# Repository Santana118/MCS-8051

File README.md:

# MCS-8051

Almost everything is written in assembly language for MCS 8051. Just copy this source file into Proteus 8 for simulating MCS 8051 component or you can upload it into your own physical MCS 8051, but make sure to convert this source file into BIN format first.

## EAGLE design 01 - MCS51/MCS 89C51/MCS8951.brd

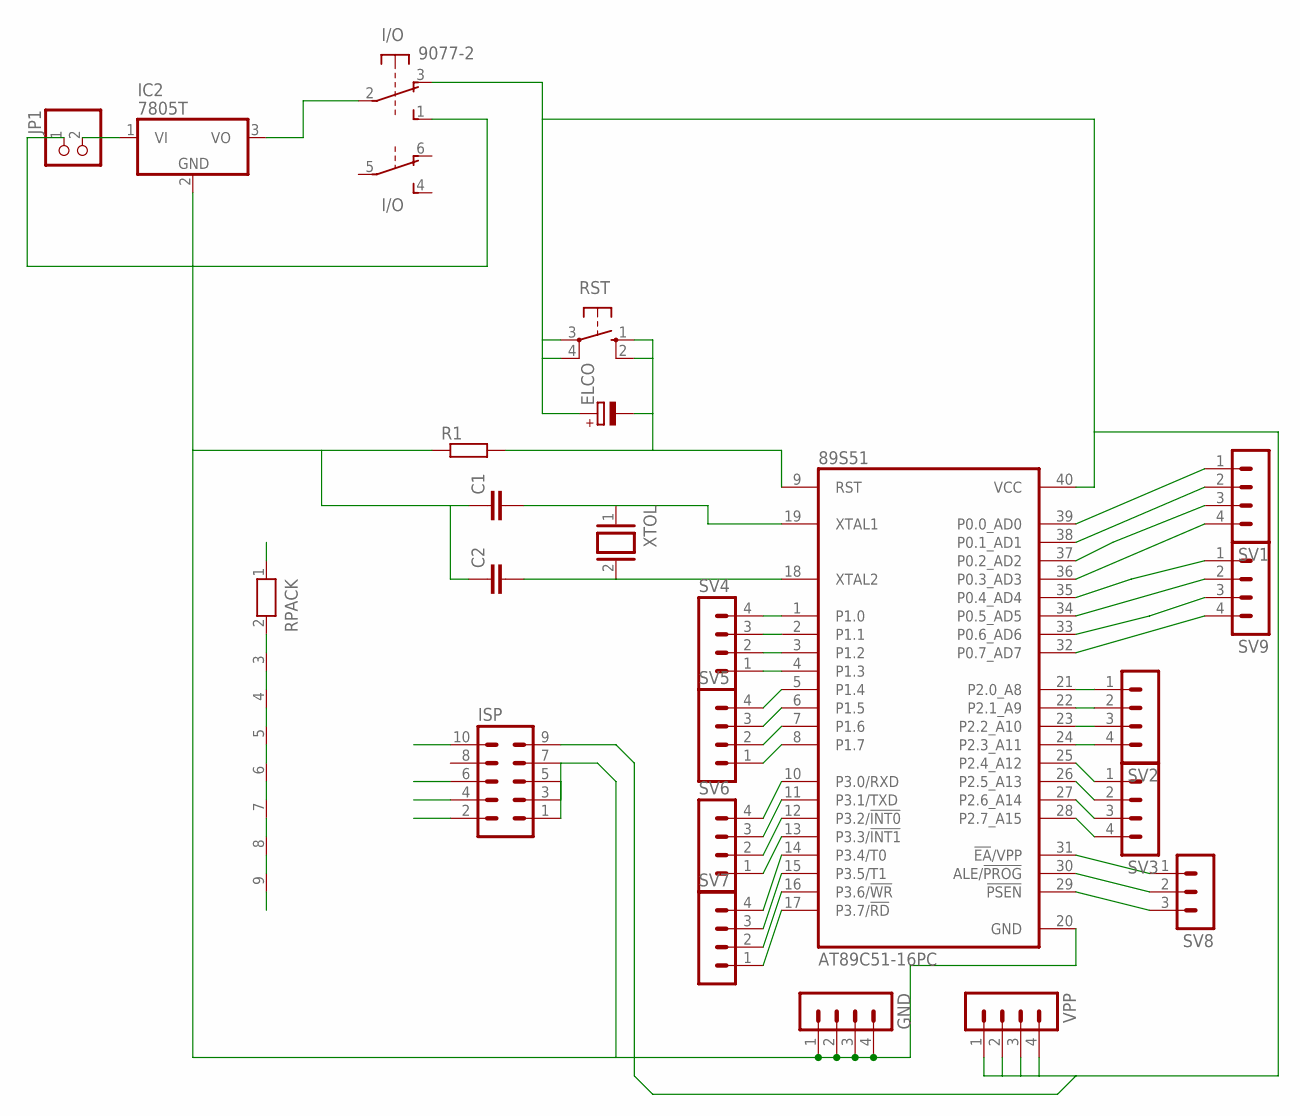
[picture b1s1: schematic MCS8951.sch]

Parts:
89S51: AT89C51-16PC; DIL40
C1, C2: C-EU025-030X050; C025-030X050
ELCO: CPOL-EUE5-5; E5-5
GND: MA04-1
I/O: 9077-2
IC2: 7805T; TO220H
ISP: MA05-2
JP1: PINHD-1X2; 1X02
R1: R-EU_0207/10; 0207/10
RPACK: RN08; RN-9
RST: 10-XX; B3F-10XX
SV1, SV2, SV3, SV4, SV5, SV6, SV7, SV9: MA04-1
SV8: MA03-1
VPP: MA04-1
XTOL: XTAL/S; QS

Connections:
GND: 89S51.20 (GND), C1.1, C2.1, GND.1, GND.2, GND.3, GND.4, I/O.1 (S), IC2.2 (GND), ISP.1, ISP.3, ISP.5, ISP.7, JP1.1, R1.1
MISO: 89S51.7 (P1.6), ISP.2, SV5.2
MOSI: 89S51.6 (P1.5), ISP.10, SV5.3
unnamed: I/O.2, IC2.3 (VO)
unnamed: 89S51.21 (P2.0_A8), SV2.1
unnamed: 89S51.22 (P2.1_A9), SV2.2
unnamed: 89S51.23 (P2.2_A10), SV2.3
unnamed: 89S51.24 (P2.3_A11), SV2.4
unnamed: 89S51.25 (P2.4_A12), SV3.1
unnamed: 89S51.26 (P2.5_A13), SV3.2
unnamed: 89S51.27 (P2.6_A14), SV3.3
unnamed: 89S51.28 (P2.7_A15), SV3.4
unnamed: 89S51.4 (P1.3), SV4.1
unnamed: 89S51.3 (P1.2), SV4.2
unnamed: 89S51.2 (P1.1), SV4.3
unnamed: 89S51.1 (P1.0), SV4.4
unnamed: 89S51.5 (P1.4), SV5.4
unnamed: 89S51.13 (P3.3/!INT1), SV6.1
unnamed: 89S51.12 (P3.2/!INT0), SV6.2
unnamed: 89S51.11 (P3.1/TXD), SV6.3
unnamed: 89S51.10 (P3.0/RXD), SV6.4
unnamed: 89S51.17 (P3.7/!RD), SV7.1
unnamed: 89S51.16 (P3.6/!WR), SV7.2
unnamed: 89S51.15 (P3.5/T1), SV7.3
unnamed: 89S51.14 (P3.4/T0), SV7.4
unnamed: 89S51.31 (!EA!/VPP), SV8.1
unnamed: 89S51.30 (ALE/!PROG), SV8.2
unnamed: 89S51.29 (!PSEN), SV8.3
unnamed: 89S51.19 (XTAL1), C1.2, XTOL.1
unnamed: IC2.1 (VI), JP1.2
unnamed: 89S51.18 (XTAL2), C2.2, XTOL.2
R1: 89S51.39 (P0.0_AD0), RPACK.2, SV1.1
R2: 89S51.38 (P0.1_AD1), RPACK.3, SV1.2
R3: 89S51.37 (P0.2_AD2), RPACK.4, SV1.3
R4: 89S51.36 (P0.3_AD3), RPACK.5, SV1.4
R5: 89S51.35 (P0.4_AD4), RPACK.6, SV9.1
R6: 89S51.34 (P0.5_AD5), RPACK.7, SV9.2
R7: 89S51.33 (P0.6_AD6), RPACK.8, SV9.3
R8: 89S51.32 (P0.7_AD7), RPACK.9, SV9.4
RST: 89S51.9 (RST), ELCO.-, ISP.6, R1.2, RST.1 (S), RST.2 (S1)
SCK: 89S51.8 (P1.7), ISP.4, SV5.1
VPP: 89S51.40 (VCC), ELCO.+, I/O.3 (O), ISP.9, RPACK.1, RST.3, RST.4 (P1), VPP.1, VPP.2, VPP.3, VPP.4

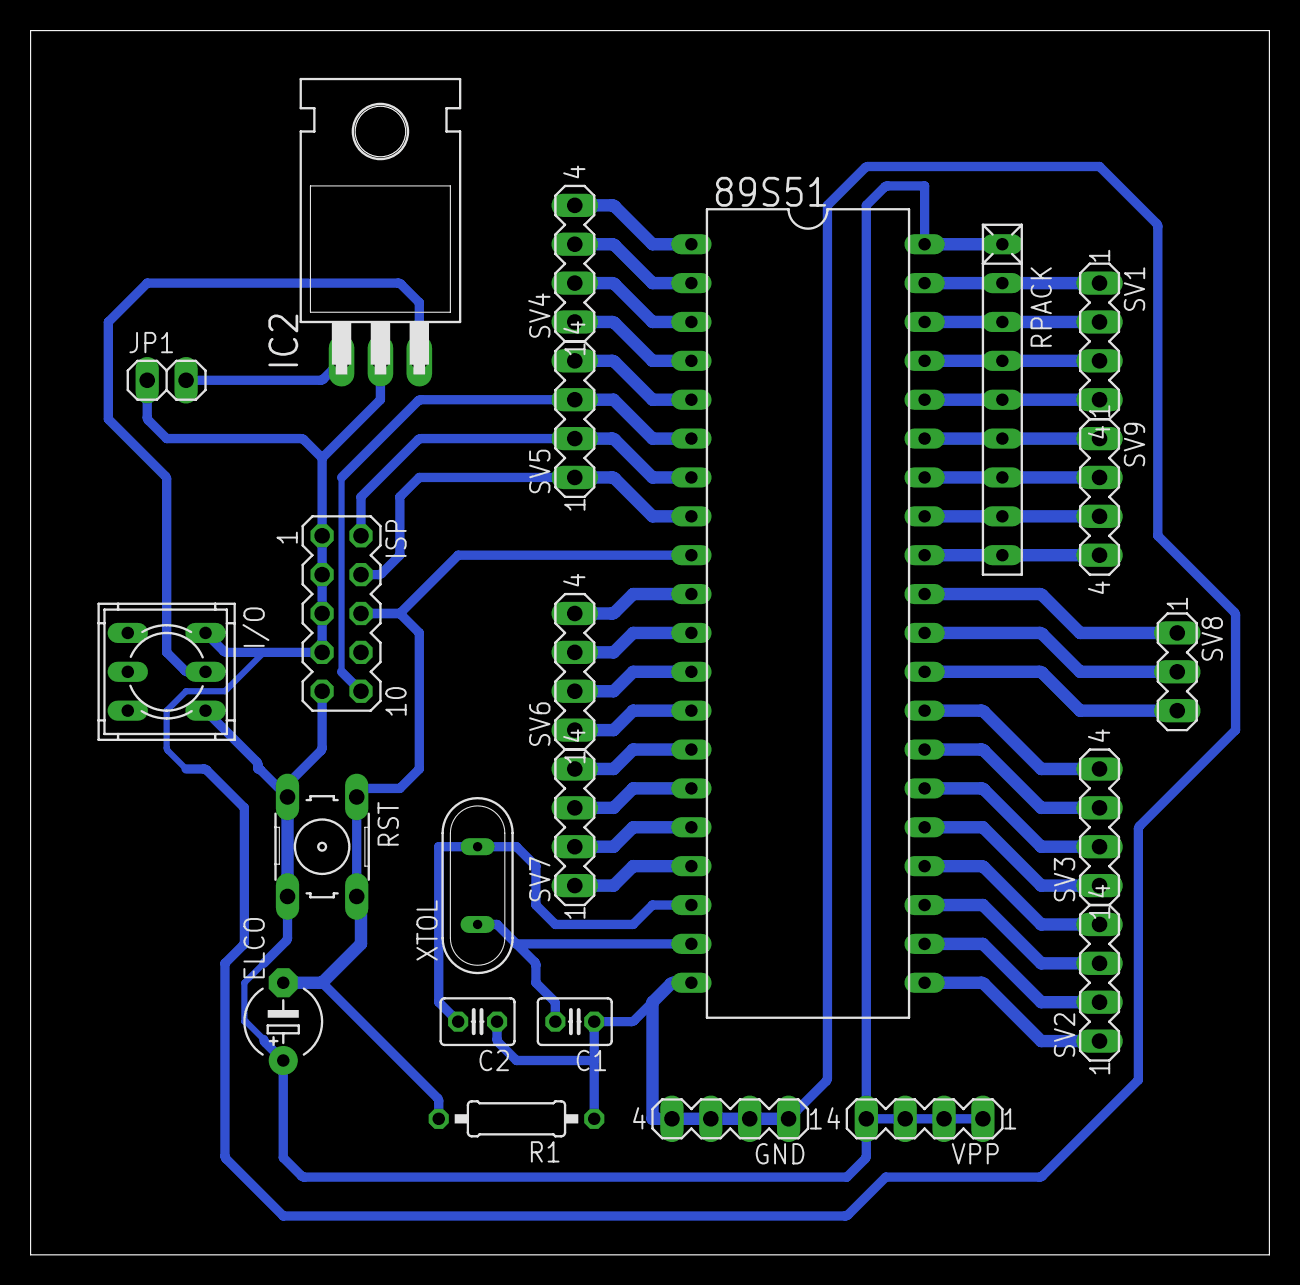
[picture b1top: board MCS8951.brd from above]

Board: 2 copper layers, 81.0 x 80.0 mm, 23 parts (0 on the bottom side), 42 nets.

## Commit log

2020-10-24 Rename 05 - Hexapod.txt to 05 - Quadruped.txt
2020-10-24 Rename 06 - Hexapod with Magnetometer.txt to 06 - Quadruped with Magnetometer.txt
2022-10-23 Restructuring all files
